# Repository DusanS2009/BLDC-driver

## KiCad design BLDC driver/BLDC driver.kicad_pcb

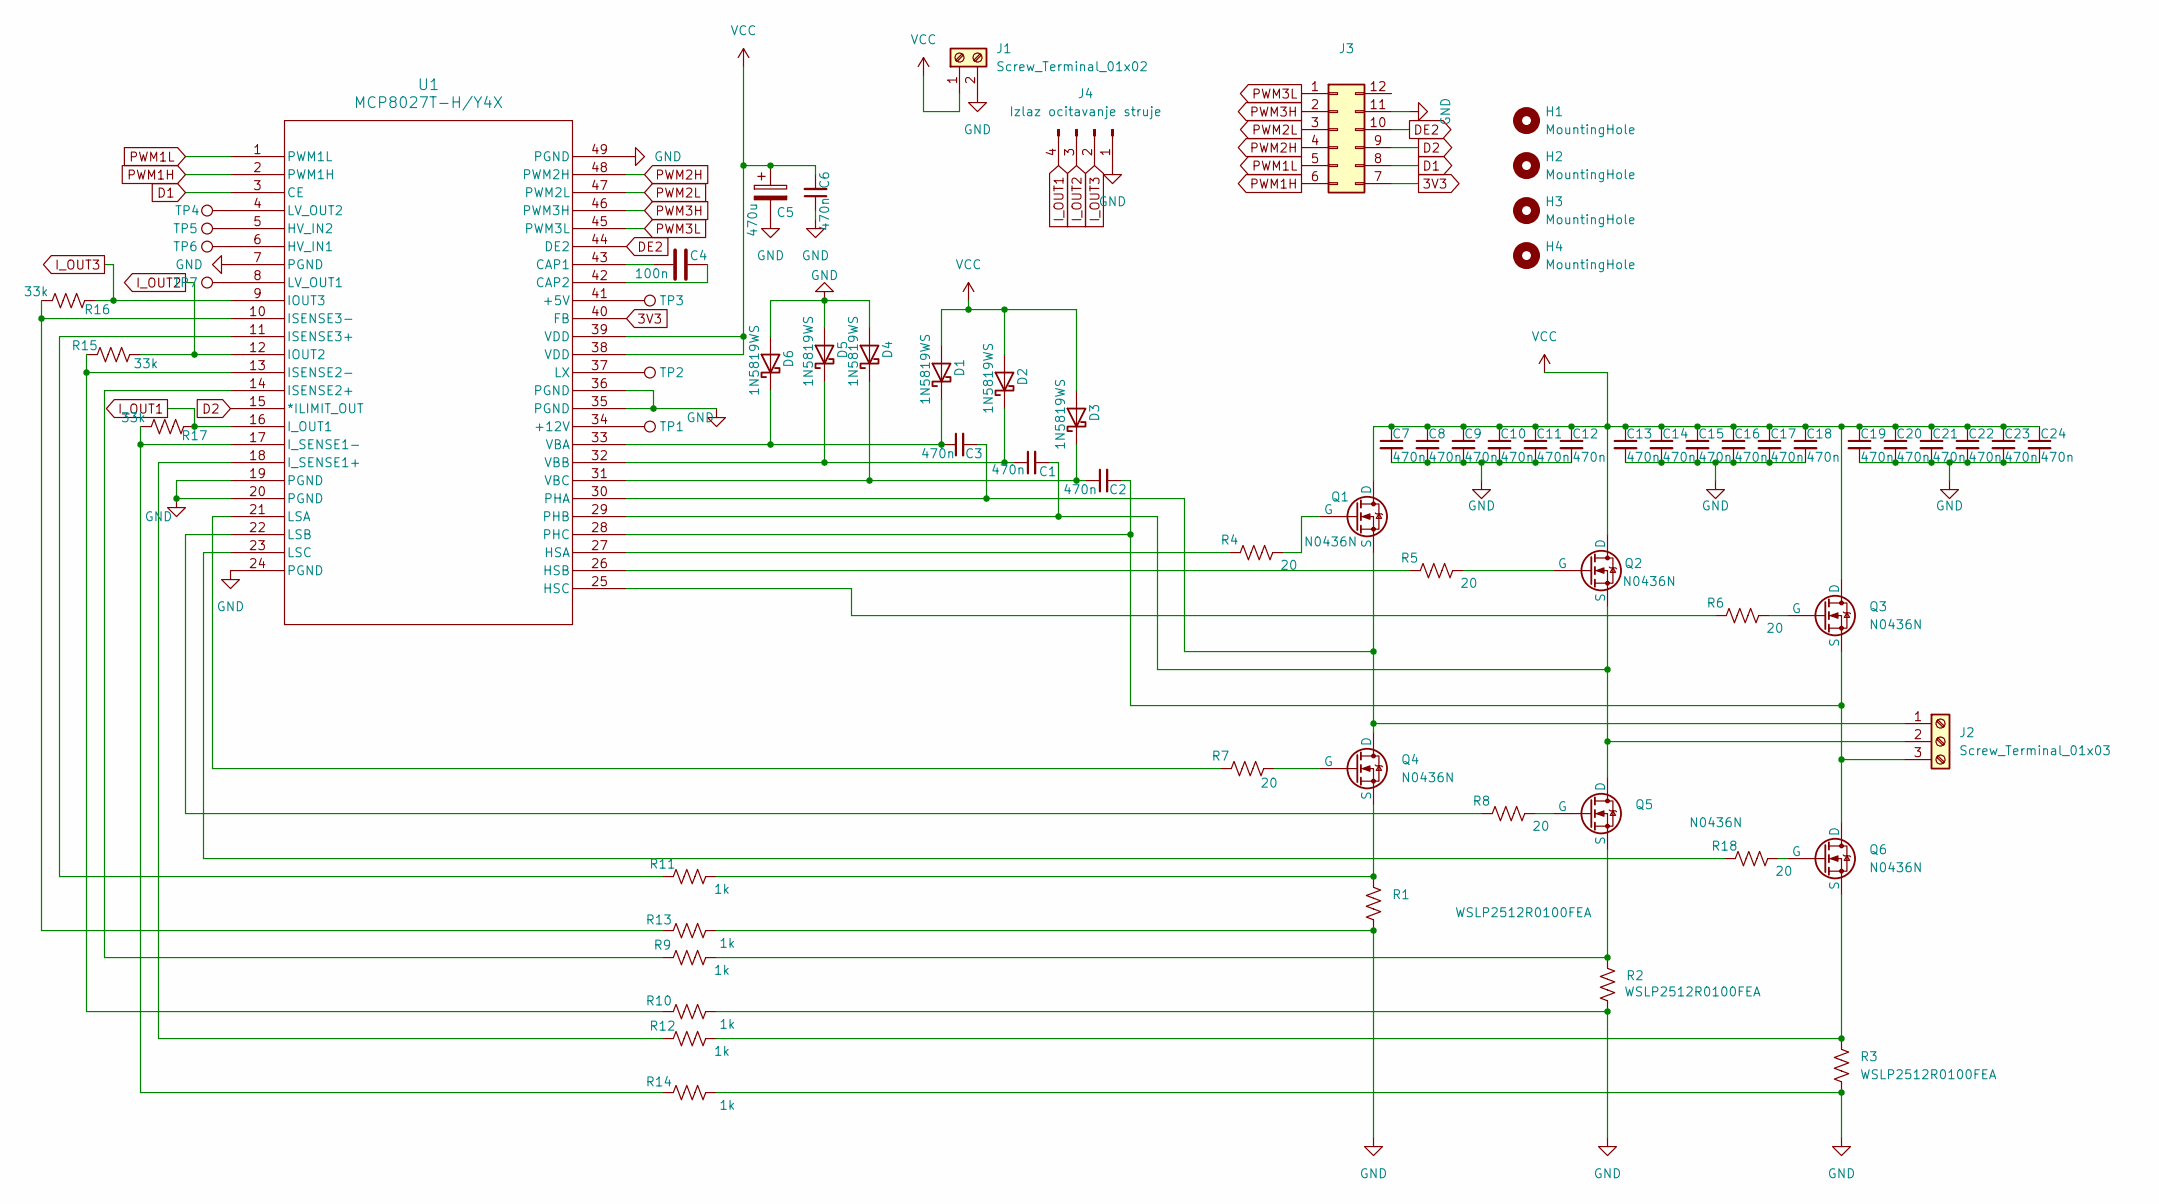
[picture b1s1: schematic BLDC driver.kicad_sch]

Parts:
C1, C2, C3, C6, C7, C8, C9, C10, C11, C12, C13, C14, C15, C16, C17, C18, C19, C20, C21, C22, C23, C24: 470n; C_0603_1608Metric_Pad1.08x0.95mm_HandSolder
C4: 100n; C_0603_1608Metric_Pad1.08x0.95mm_HandSolder
C5: 470u; CP_Radial_D10.0mm_P5.00mm
D1, D2, D3, D4, D5, D6: 1N5819WS; D_SOD-323_HandSoldering
H1, H2, H3, H4: MountingHole; MountingHole_3.2mm_M3
J1: Screw_Terminal_01x02; TerminalBlock_Phoenix_MKDS-1,5-2-5.08_1x02_P5.08mm_Horizont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
J2: Screw_Terminal_01x03; TerminalBlock_Phoenix_MKDS-1,5-3-5.08_1x03_P5.08mm_Horizont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
J3: Conn_02x06_Counter_Clockwise; PinHeader_2x06_P2.54mm_Vertical
J4: Izlaz ocitavanje struje; PinHeader_1x04_P2.54mm_Vertical
Q1, Q2, Q3, Q4, Q5, Q6: N0436N; TO-252-2
R1, R2, R3: WSLP2512R0100FEA; R_2512_6332Metric_Pad1.40x3.35mm_HandSolder
R4, R5, R6, R7, R8, R18: 20; R_0603_1608Metric_Pad0.98x0.95mm_HandSolder
R9, R10, R11, R12, R13, R14: 1k; R_0603_1608Metric_Pad0.98x0.95mm_HandSolder
R15, R16, R17: 33k; R_0603_1608Metric_Pad0.98x0.95mm_HandSolder
TP1, TP2, TP3, TP4, TP5, TP6, TP7: TestPoint; TestPoint_Pad_D3.0mm
U1: MCP8027T-H/Y4X; TQFP-48-1EP_7x7mm_P0.5mm_EP3.5x3.5mm

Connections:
3V3: J3.7, U1.40 (FB)
D1: J3.8, U1.3 (CE)
D2: J3.9, U1.15 (*ILIMIT_OUT)
DE2: J3.10, U1.44 (DE2)
GND: C5.2, C6.1, C7.2, C8.2, C9.2, C10.2, C11.2, C12.2, C13.2, C14.2, C15.2, C16.2, C17.2, C18.2, C19.2, C20.2, C21.2, C22.2, C23.2, C24.2, D4.2 (A), D5.2 (A), D6.2 (A), J1.2, J3.11, J4.1, R1.2, R2.2, R3.2, R10.2, R13.2, R14.2, U1.7 (PGND), U1.19 (PGND), U1.20 (PGND), U1.24 (PGND), U1.35 (PGND), U1.36 (PGND), U1.49 (PGND)
I_OUT1: J4.4, R17.1, U1.16 (I_OUT1)
I_OUT2: J4.3, R15.2, U1.12 (IOUT2)
I_OUT3: J4.2, R16.1, U1.9 (IOUT3)
unnamed: C3.1, D1.1 (K), D6.1 (K), U1.33 (VBA)
unnamed: C1.1, D2.1 (K), D5.1 (K), U1.32 (VBB)
unnamed: C2.1, D3.1 (K), D4.1 (K), U1.31 (VBC)
unnamed: C1.2, J2.2, Q2.3 (S), Q5.1 (D), U1.29 (PHB)
unnamed: Q1.2 (G), R4.2
unnamed: Q2.2 (G), R5.2
unnamed: Q3.2 (G), R6.2
unnamed: Q4.2 (G), R7.2
unnamed: Q4.3 (S), R1.1, R11.2
unnamed: Q5.2 (G), R8.2
unnamed: Q5.3 (S), R2.1, R9.2
unnamed: Q6.2 (G), R18.2
unnamed: Q6.3 (S), R3.1, R12.2
unnamed: TP3.1, U1.41 (+5V)
unnamed: TP1.1, U1.34 (+12V)
unnamed: C4.2, U1.43 (CAP1)
unnamed: C4.1, U1.42 (CAP2)
unnamed: R4.1, U1.27 (HSA)
unnamed: R5.1, U1.26 (HSB)
unnamed: R6.1, U1.25 (HSC)
unnamed: TP6.1, U1.6 (HV_IN1)
unnamed: TP5.1, U1.5 (HV_IN2)
unnamed: R9.1, U1.14 (ISENSE2+)
unnamed: R10.1, R15.1, U1.13 (ISENSE2-)
unnamed: R11.1, U1.11 (ISENSE3+)
unnamed: R13.1, R16.2, U1.10 (ISENSE3-)
unnamed: R12.1, U1.18 (I_SENSE1+)
unnamed: R14.1, R17.2, U1.17 (I_SENSE1-)
unnamed: R7.1, U1.21 (LSA)
unnamed: R8.1, U1.22 (LSB)
unnamed: R18.1, U1.23 (LSC)
unnamed: TP7.1, U1.8 (LV_OUT1)
unnamed: TP4.1, U1.4 (LV_OUT2)
unnamed: TP2.1, U1.37 (LX)
PWM1H: J3.6, U1.2 (PWM1H)
PWM1L: J3.5, U1.1 (PWM1L)
PWM2H: J3.4, U1.48 (PWM2H)
PWM2L: J3.3, U1.47 (PWM2L)
PWM3H: J3.2, U1.46 (PWM3H)
PWM3L: J3.1, U1.45 (PWM3L)
VCC: C5.1, C6.2, C7.1, C8.1, C9.1, C10.1, C11.1, C12.1, C13.1, C14.1, C15.1, C16.1, C17.1, C18.1, C19.1, C20.1, C21.1, C22.1, C23.1, C24.1, D1.2 (A), D2.2 (A), D3.2 (A), J1.1, Q1.1 (D), Q2.1 (D), Q3.1 (D), U1.38 (VDD), U1.39 (VDD)

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
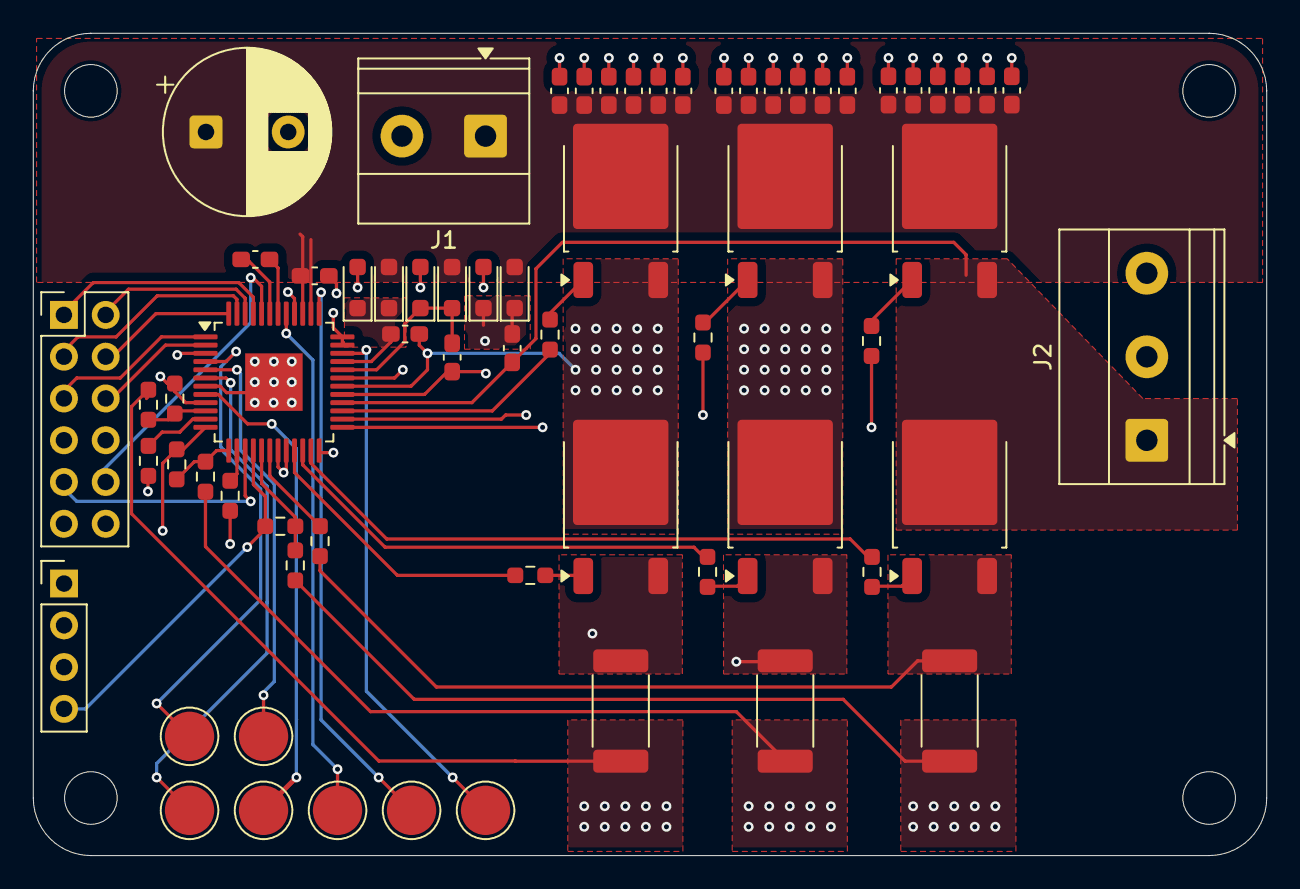
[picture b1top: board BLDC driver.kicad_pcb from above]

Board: 4 copper layers, 75.0 x 50.0 mm, 70 parts (0 on the bottom side), 51 nets.
